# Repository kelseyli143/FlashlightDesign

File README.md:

# FlashlightDesign
BME design flashlight project

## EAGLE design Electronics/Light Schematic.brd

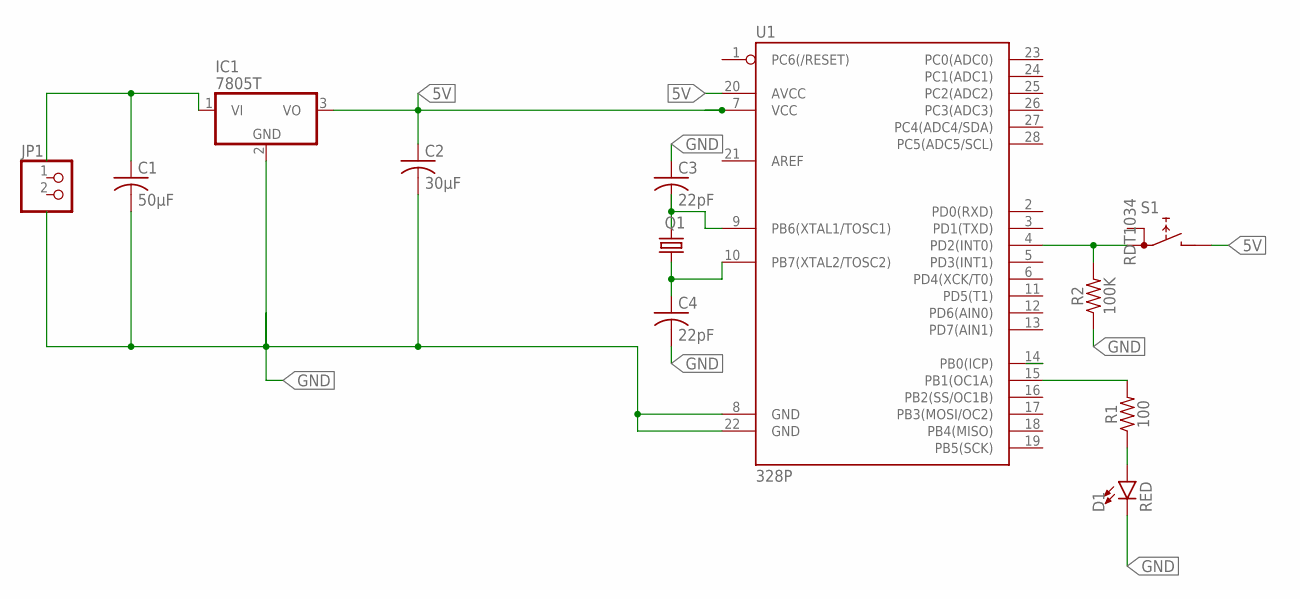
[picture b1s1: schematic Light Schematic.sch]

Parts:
C1: 50µF; C0805
C2: 30µF; C0805
C3, C4: 22pF; C0805
D1: RED; LED-0603
IC1: 7805T; TO220H
JP1: PINHD-1X2; 1X02
Q1: CRYSTALHC49S; HC49/S
R1: 100; 0402
R2: 100K; 0402
S1: RDT1034
U1: 328P; DIP28

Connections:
5V: C2.1, IC1.3 (VO), S1.B, U1.7 (VCC), U1.20 (AVCC)
GND: C1.2, C2.2, C3.1, C4.2, D1.C, IC1.2 (GND), R2.1, U1.8 (GND), U1.22 (GND)
unnamed: C1.1, IC1.1 (VI)
unnamed: R2.2, S1.A1, U1.4 (PD2(INT0))
unnamed: C3.2, Q1.2, U1.9 (PB6(XTAL1/TOSC1))
unnamed: D1.A, R1.1
unnamed: R1.2, U1.15 (PB1(OC1A))
unnamed: C4.1, Q1.1, U1.10 (PB7(XTAL2/TOSC2))

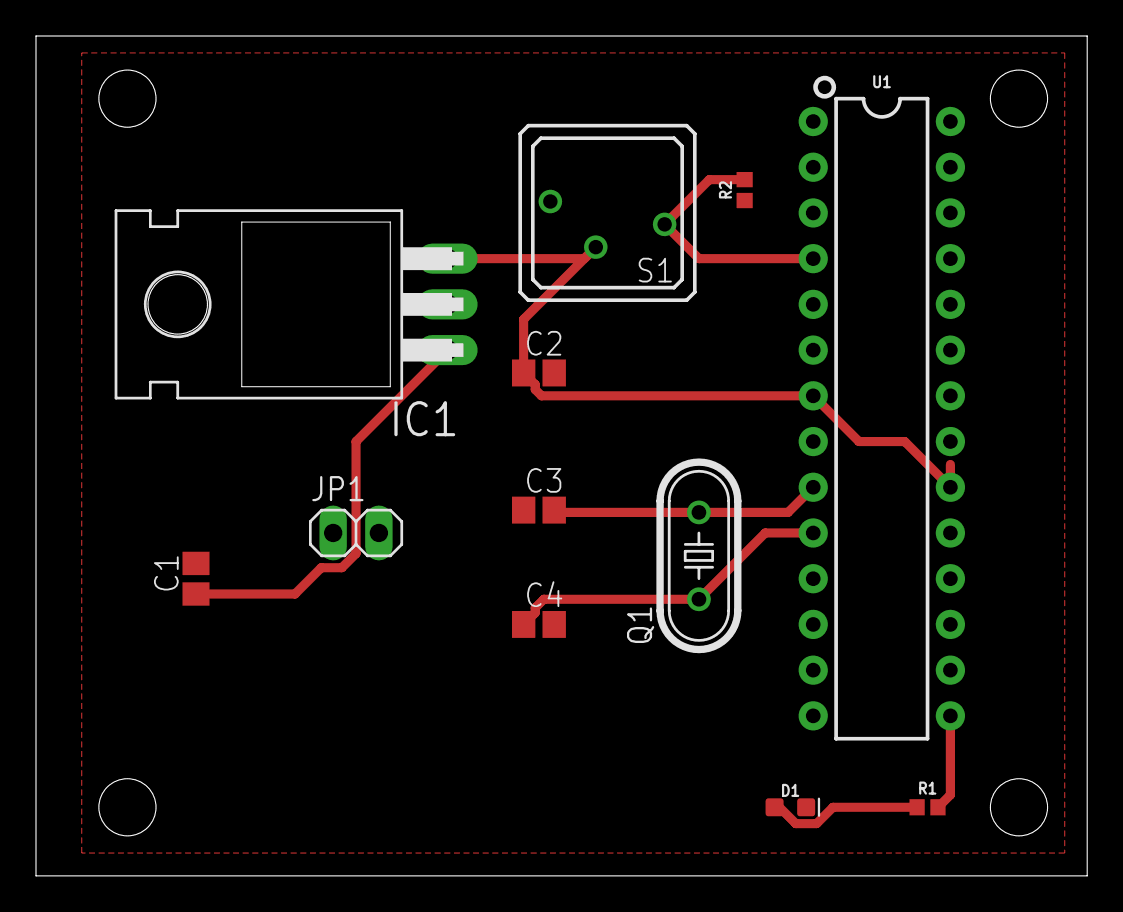
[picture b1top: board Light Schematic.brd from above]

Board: 2 copper layers, 58.4 x 46.7 mm, 12 parts (0 on the bottom side), 8 nets.

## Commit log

2018-11-01 Add files via upload
    should be under electronics but haven't made directory yet :-)
2018-11-08 Create empty
2018-11-08 Add files via upload
    EDA circuit diagram
2018-11-08 Add files via upload
    software flowchart
2018-11-08 Delete 45311652_1874406449274785_3491287341920681984_n.jpg
    old circuit diagram deleted
2018-11-12 Add files via upload
    Lightbox Arduino code
2018-11-12 Add files via upload
    new EDA circuit diagram
2018-11-13 light schematic PCB
2018-11-13 pdf of EDA circuit schematic
2018-11-13 updated light box code
2018-11-13 first light box code pre-testing
2018-11-26 updated PCB and schematic w crystal oscillator
    and 2 capacitors
2018-11-26 parts list for lightbox
2018-11-30 updated light box schematic and PCB
    - connected pin 8 and pin 22
    - changed the battery to header pins
2018-11-30 updated light box board
2018-12-12 solidworks parts for top and bottom of light box
2018-12-12 2d and 3d pdfs of solidworks light box top/bottom
2018-12-12 updated light box code after testing
2018-12-13 Create Hardware
2018-12-13 pdf of updated circuit diagram EAGLE
2018-12-13 PCB eagle updated pdf
2018-12-13 videos testing the light

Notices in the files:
parts and their libraries:
SparkFun-LED: Licensing: Creative Commons ShareAlike 4.0 International - https://creativecommons.org/licenses/by-sa/4.0
